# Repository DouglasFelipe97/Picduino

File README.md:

# Picduino Versão 2.0 #
------------------------------------------------------------------------------------------------------
Projetado e criado por Douglas Felipe 05/2021
                       -ATUALIZADO em 02/2024

Projetado na plataforma KiCad 5.19.

Programado MPLabx 5.10.

Compilador Xc8 1.30.

Linkedin https://www.linkedin.com/in/douglas-felipe-57960716a

------------------------------------------------------------------------------------------------------
Características:

Usa o pic16f877a/pic18f4550 involucro DIP40.

Para pic16f877a é necessario o uso de oscilador externo de sua escolha entre 4 e 20 MHz.

Para pic18f4550 pode ser usado o mesmo oscilador ou o oscilador interno que é disponivel nesse modelo.

A placa conta com entrada para fonte de 12V de 300mA a 1A.

1 saida de 5v e uma saida de 12v para ligação de sensores ou atuadores.

Conta com botão para Reset, e pinos para gravação, para a gravação recomendo pic kit3.

A sequencia de pinos para gravação são respectivamente : MCLR, VSS, VDD, PGC, PGD

Conta com um led ligado em catodo comum no pino RA0.

Conta com um buzzer ligado no pino RB7.

------------------------------------------------------------------------------------------------------

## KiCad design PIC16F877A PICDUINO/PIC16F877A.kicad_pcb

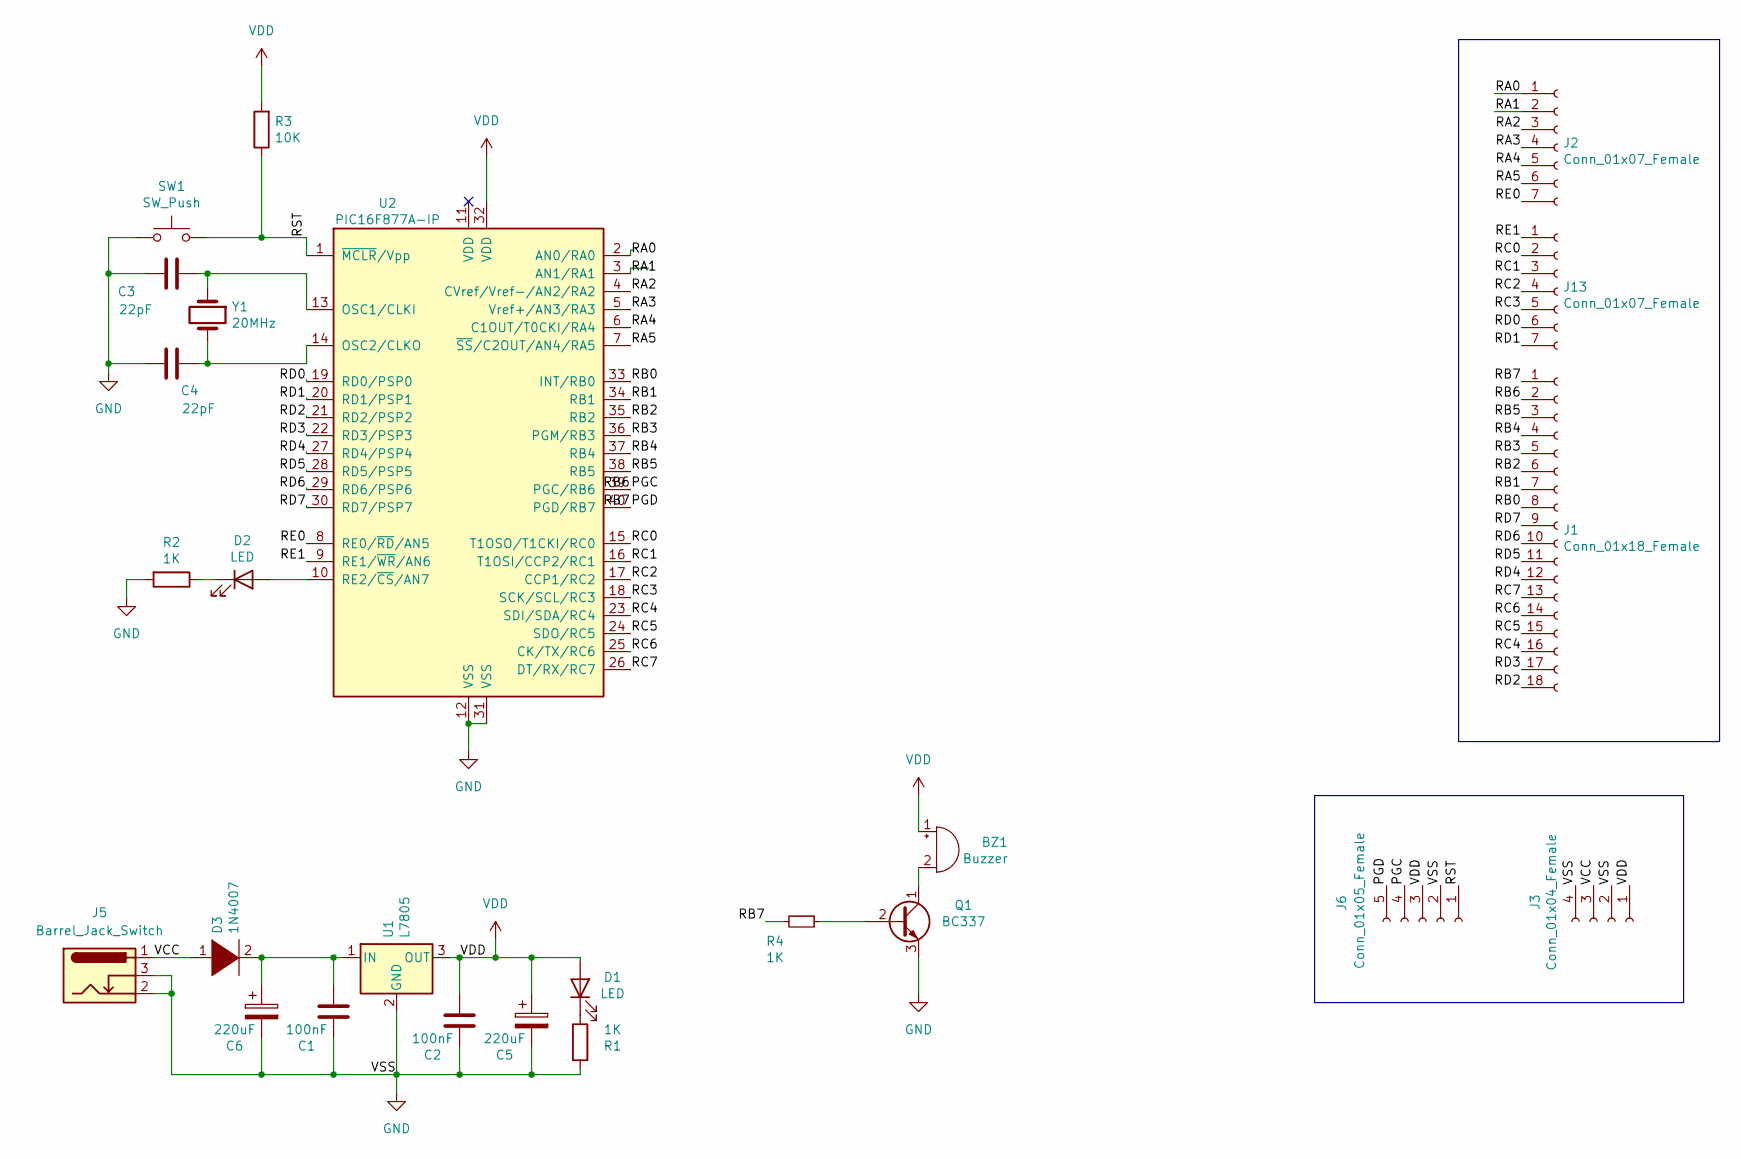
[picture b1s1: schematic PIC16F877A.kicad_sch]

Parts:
BZ1: Buzzer; Buzzer_12x9.5RM7.6
C1, C2: 100nF; C_Disc_D10.0mm_W2.5mm_P5.00mm
C3, C4: 22pF; C_Disc_D10.0mm_W2.5mm_P5.00mm
C5, C6: 220uF; CP_Radial_D10.0mm_P5.00mm
D1, D2: LED; LED_D5.0mm
D3: 1N4007; D_DO-15_P10.16mm_Horizontal
J1: Conn_01x18_Female; PinHeader_1x18_P2.54mm_Vertical
J2, J13: Conn_01x07_Female; PinHeader_1x07_P2.54mm_Vertical
J3: Conn_01x04_Female; PinHeader_1x04_P2.54mm_Vertical
J5: Barrel_Jack_Switch; BarrelJack_Horizontal
J6: Conn_01x05_Female; PinHeader_1x05_P2.54mm_Vertical
Q1: BC337; TO-92_Inline
R1, R2, R4: 1K; R_Axial_DIN0207_L6.3mm_D2.5mm_P7.62mm_Horizontal
R3: 10K; R_Axial_DIN0207_L6.3mm_D2.5mm_P7.62mm_Horizontal
SW1: SW_Push; SW_DIP_SPSTx01_Slide_9.78x4.72mm_W7.62mm_P2.54mm
U1: L7805; TO-220-3_Vertical
U2: PIC16F877A-IP; DIP-40_W15.24mm_LongPads
Y1: 20MHz; Crystal_HC49-4H_Vertical

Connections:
/PGC: J1.2, J6.4, U2.39 (PGC/RB6)
/PGD: J1.1, J6.5, R4.2, U2.40 (PGD/RB7)
/RA0: J2.1, U2.2 (AN0/RA0)
/RA1: J2.2, U2.3 (AN1/RA1)
/RA2: J2.3, U2.4 (CVref/Vref-/AN2/RA2)
/RA3: J2.4, U2.5 (Vref+/AN3/RA3)
/RA4: J2.5, U2.6 (C1OUT/T0CKI/RA4)
/RA5: J2.6, U2.7 (~SS/C2OUT/AN4/RA5)
/RB0: J1.8, U2.33 (INT/RB0)
/RB1: J1.7, U2.34 (RB1)
/RB2: J1.6, U2.35 (RB2)
/RB3: J1.5, U2.36 (PGM/RB3)
/RB4: J1.4, U2.37 (RB4)
/RB5: J1.3, U2.38 (RB5)
/RC0: J13.2, U2.15 (T1OSO/T1CKI/RC0)
/RC1: J13.3, U2.16 (T1OSI/CCP2/RC1)
/RC2: J13.4, U2.17 (CCP1/RC2)
/RC3: J13.5, U2.18 (SCK/SCL/RC3)
/RC4: J1.16, U2.23 (SDI/SDA/RC4)
/RC5: J1.15, U2.24 (SDO/RC5)
/RC6: J1.14, U2.25 (CK/TX/RC6)
/RC7: J1.13, U2.26 (DT/RX/RC7)
/RD0: J13.6, U2.19 (RD0/PSP0)
/RD1: J13.7, U2.20 (RD1/PSP1)
/RD2: J1.18, U2.21 (RD2/PSP2)
/RD3: J1.17, U2.22 (RD3/PSP3)
/RD4: J1.12, U2.27 (RD4/PSP4)
/RD5: J1.11, U2.28 (RD5/PSP5)
/RD6: J1.10, U2.29 (RD6/PSP6)
/RD7: J1.9, U2.30 (RD7/PSP7)
/RE0: J2.7, U2.8 (RE0/~RD/AN5)
/RE1: J13.1, U2.9 (RE1/~WR/AN6)
/RST: J6.1, R3.1, SW1.2, U2.1 (~MCLR/Vpp)
/VCC: D3.1 (K), J3.3, J5.1
GND: C1.2, C2.2, C3.2, C4.2, C5.2, C6.2, J3.2, J3.4, J5.2, J5.3, J6.2, Q1.3 (E), R1.2, R2.2, SW1.1, U1.2 (GND), U2.12 (VSS), U2.31 (VSS)
unnamed: BZ1.2 (+), Q1.1 (C)
unnamed: D1.1 (K), R1.1
unnamed: D2.2 (A), U2.10 (RE2/~CS/AN7)
unnamed: D2.1 (K), R2.1
unnamed: C1.1, C6.1, D3.2 (A), U1.1 (IN)
unnamed: Q1.2 (B), R4.1
unnamed: C3.1, U2.13 (OSC1/CLKI), Y1.1
unnamed: C4.1, U2.14 (OSC2/CLKO), Y1.2
VDD: BZ1.1 (-), C2.1, C5.1, D1.2 (A), J3.1, J6.3, R3.2, U1.3 (OUT), U2.32 (VDD)

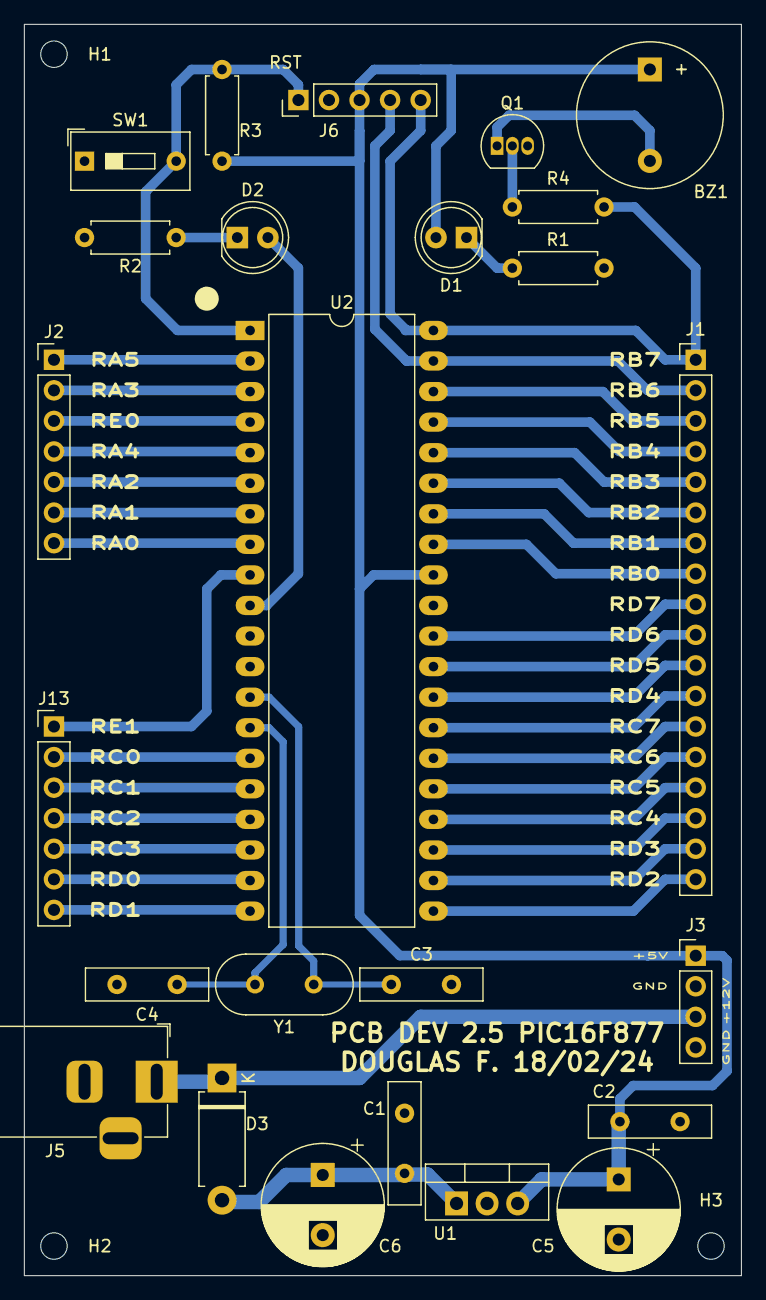
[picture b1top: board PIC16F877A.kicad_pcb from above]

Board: 2 copper layers, 59.6 x 104.0 mm, 28 parts (0 on the bottom side), 44 nets.

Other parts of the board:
H1, H2, H3: MountingHole_2.2mm_M2

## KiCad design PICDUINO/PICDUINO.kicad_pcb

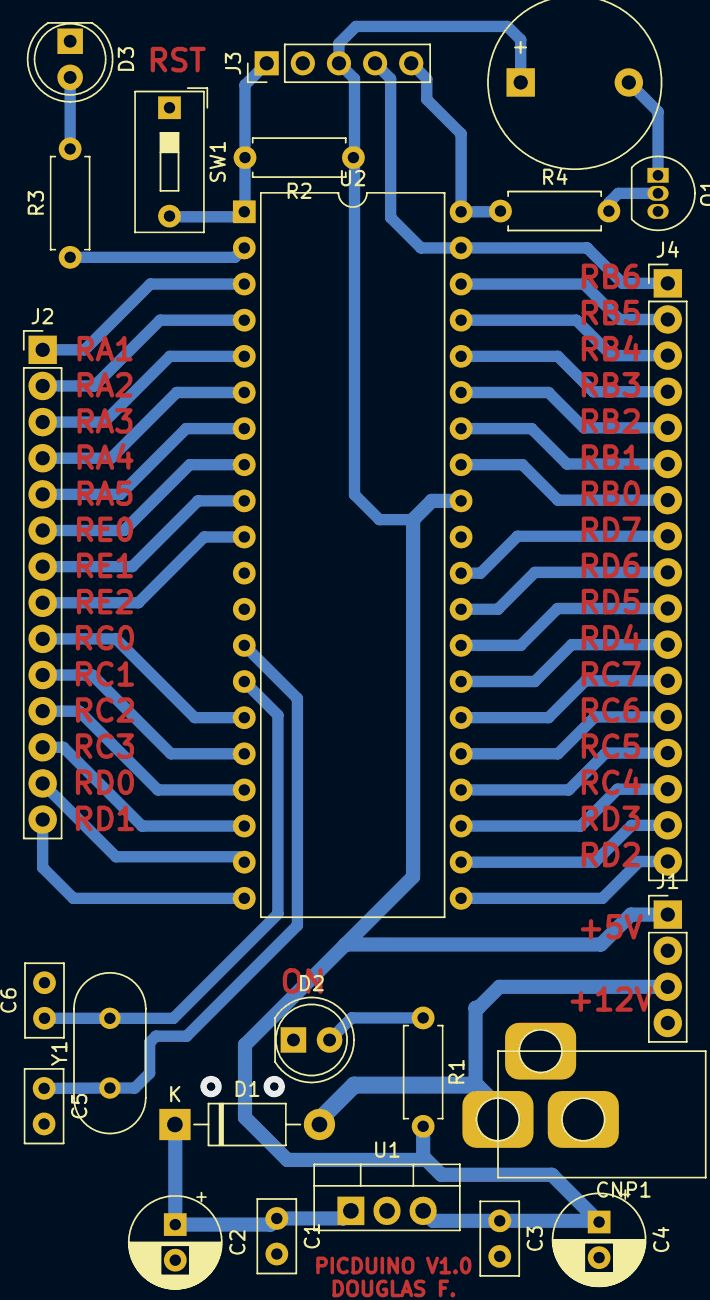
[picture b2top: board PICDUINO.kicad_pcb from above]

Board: 2 copper layers, 24 parts (0 on the bottom side), 44 nets.

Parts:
BZ1: Buzzer; Buzzer_12x9.5RM7.6
C1: 330nF; C_Disc_D5.0mm_W2.5mm_P2.50mm
C2, C4: 220uF; CP_Radial_D6.3mm_P2.50mm
C3: 100nF; C_Disc_D5.0mm_W2.5mm_P2.50mm
C5, C6: 22pF; C_Disc_D5.0mm_W2.5mm_P2.50mm
CNP1: P4Femea; ConnP4
D1: 1n4007; D_DO-41_SOD81_P10.16mm_Horizontal
D2, D3: LED; LED_D5.0mm
J1: Conn_01x04_Female; PinHeader_1x04_P2.54mm_Vertical
J2: Conn_01x14_Female; PinHeader_1x14_P2.54mm_Vertical
J3: Conn_01x05_Male; PinHeader_1x05_P2.54mm_Vertical
J4: Conn_01x20_Female; PinHeader_1x17_P2.54mm_Vertical
Q1: BC337; TO-92_Inline
R1, R3: 560R; R_Axial_DIN0207_L6.3mm_D2.5mm_P7.62mm_Horizontal
R2: 10K; R_Axial_DIN0207_L6.3mm_D2.5mm_P7.62mm_Horizontal
R4: 1K; R_Axial_DIN0207_L6.3mm_D2.5mm_P7.62mm_Horizontal
SW1: SW_Push; SW_DIP_SPSTx01_Slide_9.78x4.72mm_W7.62mm_P2.54mm
U1: L7805; TO-220-3_Vertical
U2: PIC16F877A-IP; DIP-40_W15.24mm
Y1: Crystal; Crystal_HC18-U_Vertical

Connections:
/MCLR: J3.1, R2.2, SW1.2, U2.1
/PGC: J3.4, J4.1, U2.39
/PGD: J3.5, R4.1, U2.40
/RA1: J2.1, U2.3
/RA2: J2.2, U2.4
/RA3: J2.3, U2.5
/RA4: J2.4, U2.6
/RA5: J2.5, U2.7
/RB0: J4.7, U2.33
/RB1: J4.6, U2.34
/RB2: J4.5, U2.35
/RB3: J4.4, U2.36
/RB4: J4.3, U2.37
/RB5: J4.2, U2.38
/RC0: J2.9, U2.15
/RC1: J2.10, U2.16
/RC2: J2.11, U2.17
/RC3: J2.12, U2.18
/RC4: J4.15, U2.23
/RC5: J4.14, U2.24
/RC6: J4.13, U2.25
/RC7: J4.12, U2.26
/RD0: J2.13, U2.19
/RD1: J2.14, U2.20
/RD2: J4.17, U2.21
/RD3: J4.16, U2.22
/RD4: J4.11, U2.27
/RD5: J4.10, U2.28
/RD6: J4.9, U2.29
/RD7: J4.8, U2.30
/RE0: J2.6, U2.8
/RE1: J2.7, U2.9
/RE2: J2.8, U2.10
/VCC: CNP1.VCC, D1.1, J1.3
/VDD: BZ1.1, C3.1, C4.1, J1.1, J3.3, R1.2, R2.1, U1.3, U2.32
/VSS: C1.2, C2.2, C3.2, C4.2, C5.2, C6.2, CNP1.GND, D2.1, D3.1, J1.2, J1.4, J3.2, Q1.3, SW1.1, U1.2, U2.12, U2.31
unnamed: BZ1.2, Q1.1
unnamed: C1.1, C2.1, D1.2, U1.1
unnamed: C5.1, U2.13, Y1.1
unnamed: C6.1, U2.14, Y1.2
unnamed: D2.2, R1.1
unnamed: D3.2, R3.2
unnamed: Q1.2, R4.2
unnamed: R3.1, U2.2

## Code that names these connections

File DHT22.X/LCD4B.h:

#include <xc.h> // include processor files - each processor file is guarded.



  
    // ========================================================================================//
    //Definição de configurações
    // ========================================================================================//

    //Cristal Oscilador - Frequencia
    #ifndef XTAL_FREQ
        #define _XTAL_FREQ 20000000
    #endif
    //Pinos para Display LCD
    
        #define RS PORTBbits.RB0  
        #define EN PORTBbits.RB1  
        #define D4 PORTBbits.RB2
        #define D5 PORTBbits.RB3
        #define D6 PORTBbits.RB4
        #define D7 PORTBbits.RB5
 
    
	
	//Prototipos de função
	
	
            void LCD_Init();                   /*Initialize LCD*/
            void LCD_Command(unsigned char );  /*Send command to LCD*/
            void LCD_Char(unsigned char x);    /*Send data to LCD*/
            void LCD_String(const char *);     /*Display data string on LCD*/
            void LCD_String_xy(char, char , const char *);
            void LCD_Char_xy(char row,char pos,unsigned char dat);
            void LCD_Clear();                  /*Clear LCD Screen*/

	

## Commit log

2021-06-20 Add files via upload
    Camada superior e inferior para a impressão a confecção caseira da placa.
2021-06-20 Add files via upload
    Programa para teste MPLabX
2022-02-15 Add files via upload
    Utilizando portas simultâneas do conversor AD PIC18F4550
